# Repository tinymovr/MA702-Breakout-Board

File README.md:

# MA702-Breakout Board

Simple example of using the [MA702 breakout board](https://tinymovr.com/collections/all/products/ma702-breakout) with Arduino.

The project can be directly opened and built using PlatformIO.
Monitor baud rate is 115200.

Board schematic and layout files are in [hardware/](./hardware)

An example usable with the Arduino IDE is in [Arduino/](./Arduino)

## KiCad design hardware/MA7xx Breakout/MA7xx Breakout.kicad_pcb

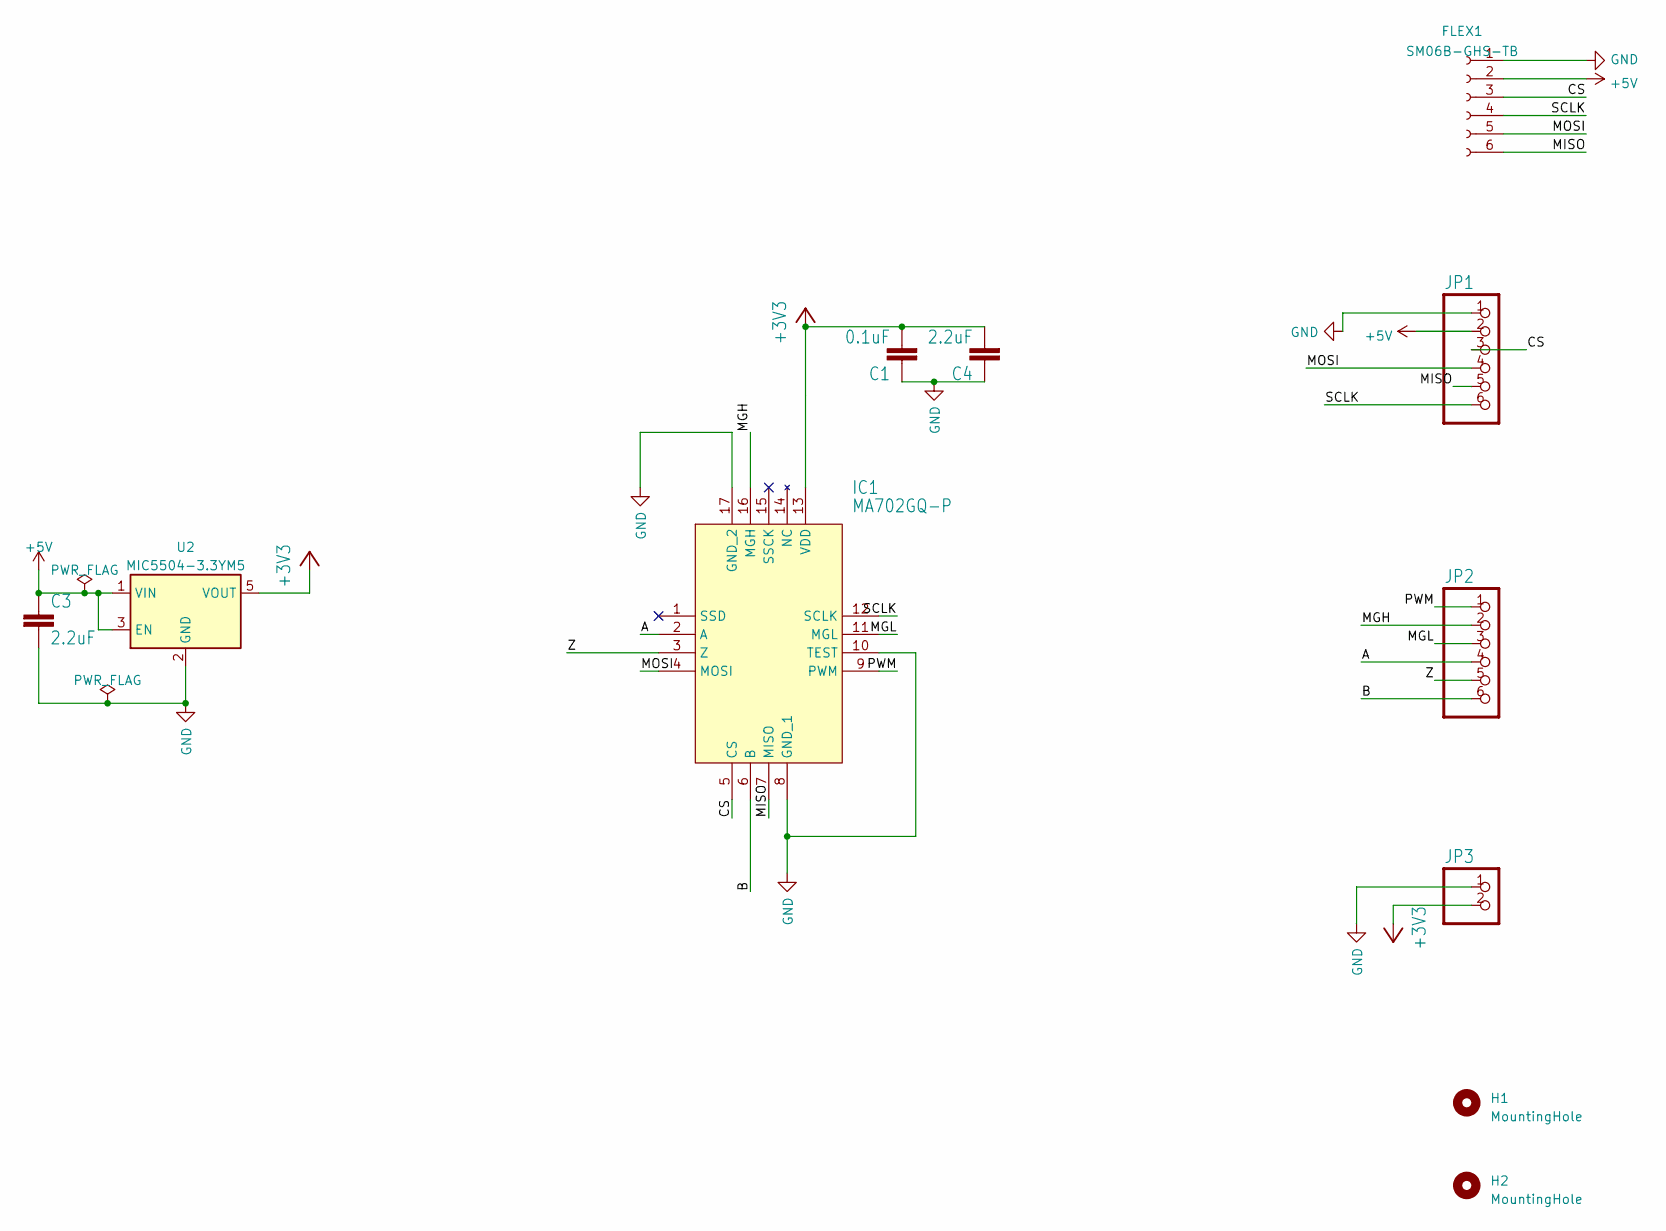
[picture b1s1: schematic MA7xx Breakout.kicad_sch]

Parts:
C1: 0.1uF; C_0402_1005Metric
C3, C4: 2.2uF; C_0603_1608Metric
FLEX1: SM06B-GHS-TB; JST_GH_SM06B-GHS-TB_1x06-1MP_P1.25mm_Horizontal
H1, H2: MountingHole; MountingHole_2.7mm_M2.5_DIN965
IC1: MA702GQ-P; QFN-16-1EP_3x3mm_P0.5mm_EP1.7x1.7mm
JP1, JP2: PINHD-1X06_2.54-S; 1X06-S
JP3: PINHD-1X02_2.54-S; 1X02-S
U2: MIC5504-3.3YM5; SOT-23-5

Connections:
+3V3: C1.2, C4.2, IC1.13 (VDD), JP3.2, U2.5 (VOUT)
+5V: C3.1, FLEX1.2, JP1.2, U2.1 (VIN), U2.3 (EN)
/A: IC1.2 (A), JP2.4
/B: IC1.6 (B), JP2.6
/CS: FLEX1.3, IC1.5 (CS), JP1.3
/MGH: IC1.16 (MGH), JP2.2
/MGL: IC1.11 (MGL), JP2.3
/MISO: FLEX1.6, IC1.7 (MISO), JP1.5
/MOSI: FLEX1.5, IC1.4 (MOSI), JP1.4
/PWM: IC1.9 (PWM), JP2.1
/SCLK: FLEX1.4, IC1.12 (SCLK), JP1.6
/Z: IC1.3 (Z), JP2.5
GND: C1.1, C3.2, C4.1, FLEX1.1, IC1.8 (GND_1), IC1.10 (TEST), IC1.17 (GND_2), JP1.1, JP3.1, U2.2 (GND)

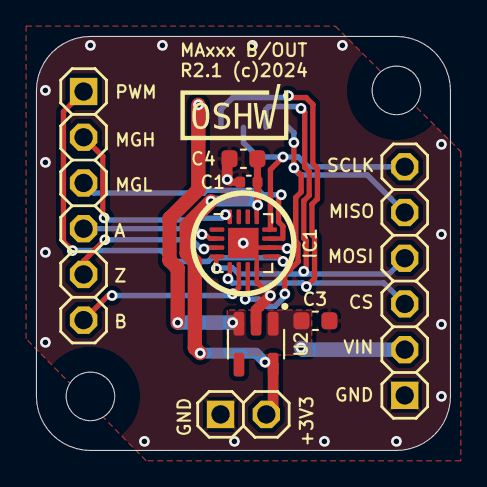
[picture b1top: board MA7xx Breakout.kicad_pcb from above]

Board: 2 copper layers, 23.0 x 23.0 mm, 11 parts (1 on the bottom side), 13 nets.

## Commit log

2020-10-25 Create LICENSE
2020-10-25 add schematics
2021-04-11 Reduce SPI rate
2024-04-03 update board revision
2024-04-03 add hw license
2024-04-03 update license
2024-04-03 add gitignore
2024-04-03 add Arduino code
2024-06-06 ignore files

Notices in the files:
hardware/MA7xx Breakout/MA7xx Breakout.kicad_pcb:
R2.1 (c)2024
